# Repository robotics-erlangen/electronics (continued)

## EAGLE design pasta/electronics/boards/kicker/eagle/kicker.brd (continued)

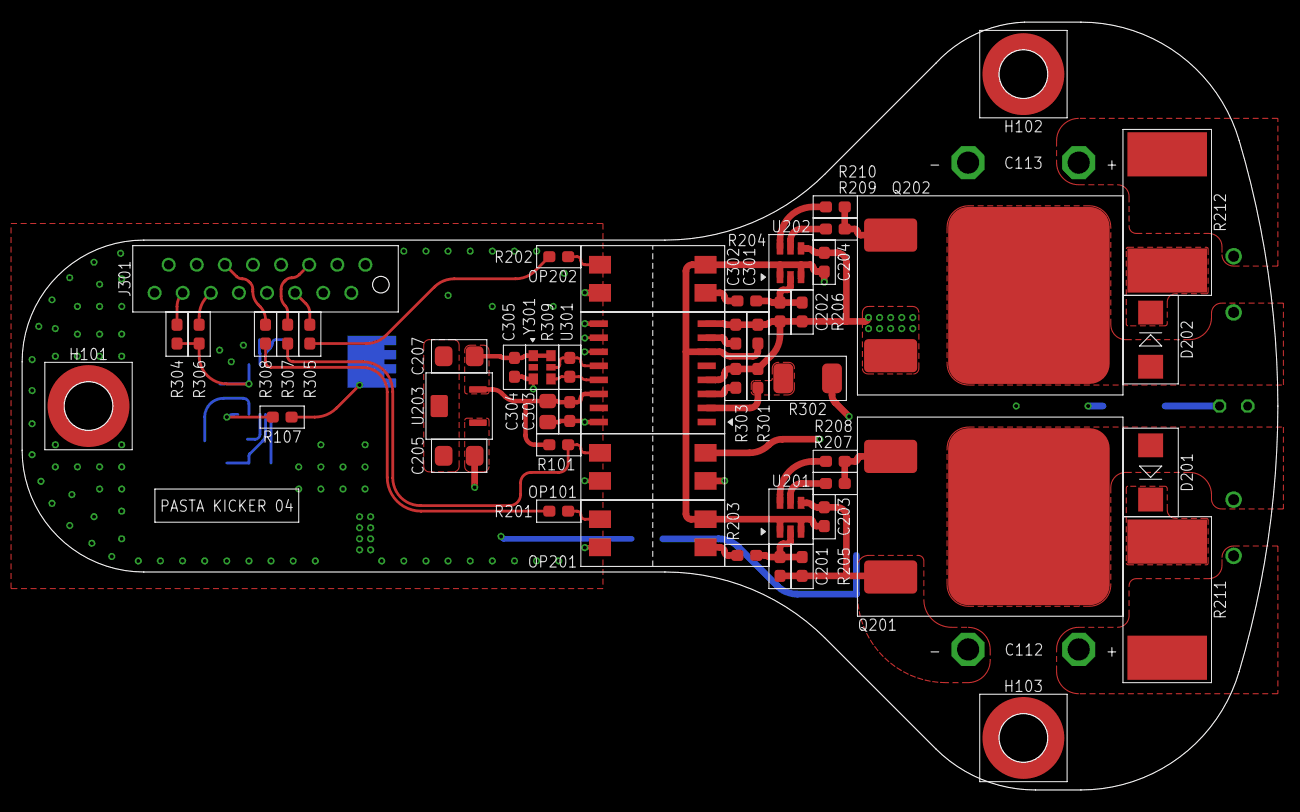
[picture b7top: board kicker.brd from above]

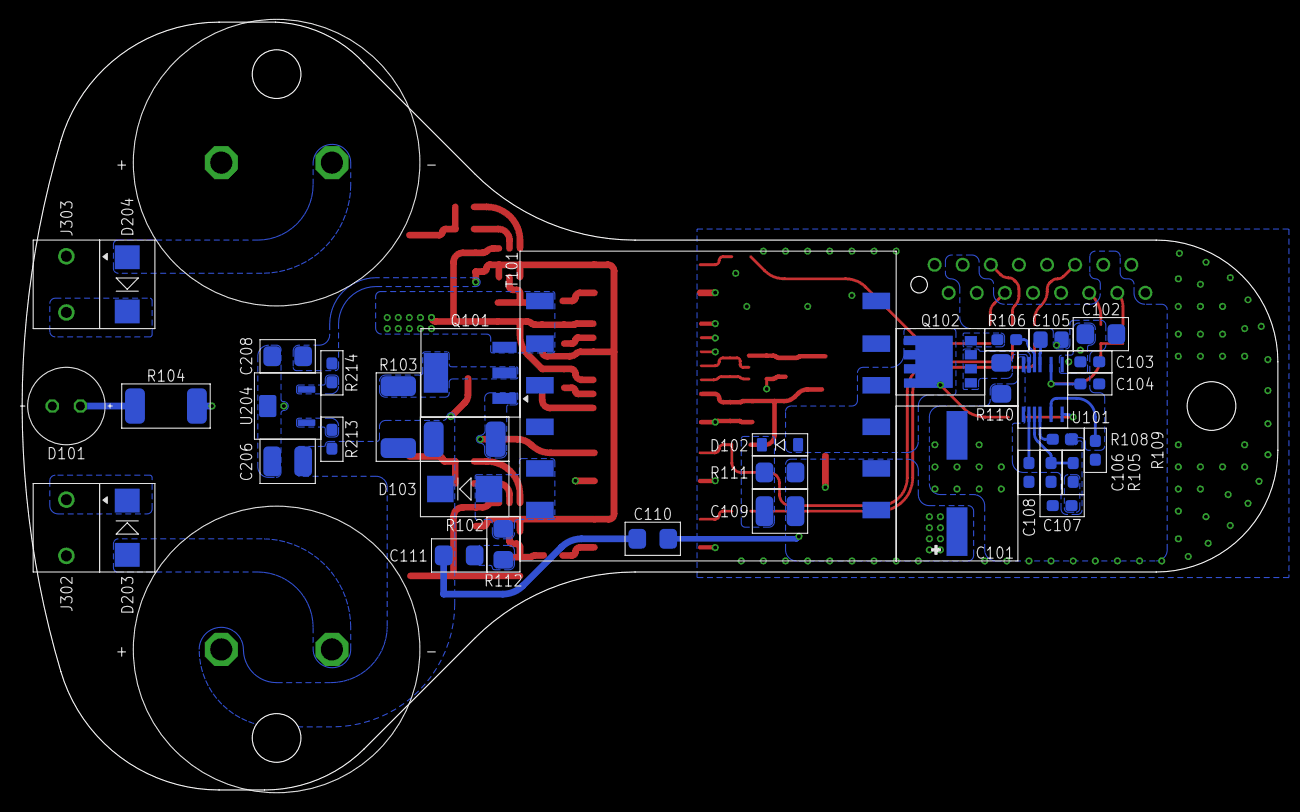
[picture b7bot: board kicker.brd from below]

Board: 4 copper layers, 113.5 x 69.4 mm, 89 parts (37 on the bottom side), 56 nets.

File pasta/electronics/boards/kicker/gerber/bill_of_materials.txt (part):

Part  Value                  MF                           MPN                 MOUSER               RESISTANCE POWER CAPACITANCE DIELECTRIC TOLERANCE VOLTAGE
C101  270  µF                Würth Elektronik             875075661009                                                                     ±10%      35V(DC)
C102  10u ±20% 50V X5R       Samsung                      CL31A106MBHNNNE                                           10u         X5R        ±20%      50V    
C103  100n ±10% 50V X7R      Würth Elektronik             885012206095                                              100n        X7R        ±10%      50V    
C104  100n ±10% 50V X7R      Würth Elektronik             885012206095                                              100n        X7R        ±10%      50V    
C105  4u7 ±10% 50V X5R       Samsung                      CL21A475KBQNNNE                                           4u7         X5R        ±10%      50V    
C106  100p ±5% 50V NP0       Würth Elektronik             885012006057                                              100p        NP0        ±5%       50V    
C107  2n2 ±10% 50V X7R       Würth Elektronik             885012206085                                              2n2         X7R        ±10%      50V    
C108  33n ±10% 50V X7R       Würth Elektronik             885012206092                                              33n         X7R        ±10%      50V    
C109                         KEMET                        C0805C224J1RECTU                                          220nF       X7R        ±5%       100V   
C110  n.c.                                                                                                          n.c.                                    
C111  n.c.                                                                                                          n.c.                                    
C112  1000u 250V             United Chemi-Con             ESMQ251VSN102MQ45S  661-ESMQ251VSN102MQ4                                                          
C113  1000u 250V             United Chemi-Con             ESMQ251VSN102MQ45S  661-ESMQ251VSN102MQ4                                                          
C201  47n ±10% 50V X7R       Würth Elektronik             885012206093                                              47n         X7R        ±10%      50V    
C202  47n ±10% 50V X7R       Würth Elektronik             885012206093                                              47n         X7R        ±10%      50V    
C203  1u ±10% 50V X5R        Samsung                      CL10A105KB8NNNC                                           1u          X5R        ±10%      50V    
C204  1u ±10% 50V X5R        Samsung                      CL10A105KB8NNNC                                           1u          X5R        ±10%      50V    
C205                         TDK                          C3225X7T2E334K200AA                                       330n        X7T        ±10%      250V   
C206                         TDK                          C3225X7T2E334K200AA                                       330n        X7T        ±10%      250V   
C207  10u ±20% 50V X5R       Samsung                      CL31A106MBHNNNE                                           10u         X5R        ±20%      50V    
C208  10u ±20% 50V X5R       Samsung                      CL31A106MBHNNNE                                           10u         X5R        ±20%      50V    
C301  100n ±10% 50V X7R      Würth Elektronik             885012206095                                              100n        X7R        ±10%      50V    
C302  100n ±10% 50V X7R      Würth Elektronik             885012206095                                              100n        X7R        ±10%      50V    
C303  100n ±10% 50V X7R      Würth Elektronik             885012206095                                              100n        X7R        ±10%      50V    
C304  2u2 ±10% 50V X7R       Samsung                      CL21B225KBYNNWE                                           2u2         X7R        ±10%      50V    
C305  100n ±10% 50V X7R      Würth Elektronik             885012206095                                              100n        X7R        ±10%      50V    
D101                         Würth Elektronik             151054RS03000                                                                                     
D102  1N4148                 Micro Commercial Components  1N4148W                                                                                           
D103  STTH212U               STMicroelectronics           STTH212U                                                                                          
D201  GB01SLT12-214          GeneSiC                      GB01SLT06-214       905-GB01SLT06-214                                                             
D202  GB01SLT12-214          GeneSiC                      GB01SLT06-214       905-GB01SLT06-214                                                             
D203  GB01SLT12-214          GeneSiC                      GB01SLT06-214       905-GB01SLT06-214                                                             
D204  GB01SLT12-214          GeneSiC                      GB01SLT06-214       905-GB01SLT06-214                                                             
H101                         Würth Elektronik             9774060360R                                                                                       
H102                         Würth Elektronik             9774060360R                                                                                       
H103                         Würth Elektronik             9774060360R                                                                                       
J301                         Würth Elektronik             690367181672                                                                                      
J302                         Würth Elektronik             66100311622                                                                                       
J303                         Würth Elektronik             66100311622                                                                                       
OP101 LTV352T                Lite-On                      LTV-816S            859-LTV-816S                                                                  
OP201 LTV352T                Lite-On                      LTV-816S            859-LTV-816S                                                                  
OP202 LTV352T                Lite-On                      LTV-816S            859-LTV-816S                                                                  
Q101  FJT44TF                onsemi / Fairchild           FJT44TF                                                                                           
Q102  TPH3300CNH             Toshiba                      TPH3300CNH          757-TPH3300CNHL1Q                                                             
Q201  IXYT55N120A4HV         IXYS                         IXYT55N120A4HV      747-IXYT55N120A4HV                                                            
Q202  IXYT55N120A4HV         IXYS                         IXYT55N120A4HV      747-IXYT55N120A4HV                                                            
R101  270R ±1% 75V 0.1W      YAGEO                        RC0603FR-07270RL                         270R       0.1W                         ±1%       75V    
R102                         TE Connectivity / Holsworthy CRGP2512F330K                            330k       2W                           ±1%       500V   
R103                         TE Connectivity / Holsworthy CRGP2512F33K                             33k        2W                           1%        500V   
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
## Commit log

2023-01-29 pasta: kicker: add version 4
2023-01-29 misc: create readme
2023-02-18 pasta: kicker: fix some bugs in schematics
    - U203 had the wrong MPN (now replaced by a 3V3 LDO)
    - Increased input capacitor of U203 to 10u 50V (previously 330n 250V)
    - Changed title of U203 block in schematics to be more fitting
    - Fixed MPN of optocouplers (value was right, but MPN was wrong)
2023-06-26 pasta: add mechanics
2023-07-04 pasta: add remaining electronics
